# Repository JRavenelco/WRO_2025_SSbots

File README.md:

# Introduction

We are the SSBots team from Mexico, competitors in the WRO Future Engineers category. This is our first year competing in this category, exploring further into WRO after competing for years in the Robo Mission Category. The purpose of this repository is to document our efforts during the 2025 season.

## The team
>Team members
- Sebastian Esquivel
- Santiago Mansilla
>Coach
- Luis Ernesto Fernandez Rodriguez

## Past experiences

  **Our team has participated in WRO Robo Mission competitions for a few years,** as to explore further into new challenges like autonomous vehicles and artificial vision,  we could carry over developments from **RoboMission** . Some of the topics were:
  - Vehicle design and instrumentation, (embedding sensors and actuators while designing purpose built hardware for the specific task.
  - Coding experience, like making a framework, carrying over and porting Python and C code for the LEGO Mindstorms.
  - PID control, implementation and tuning.
  - Path planning, obstacle detection and avoidance. 

Even though we faced multiple difficulties with development and integration of new technologies onto our Robot, while exploring onto the use of electronics for hardware design and training our own AI model for real-time vision, object detection and labeling, and decision making, in addition to all the difficulties that are still to come, we have managed to overcome these difficulties and solve this challenges. We plan on innovating and improving even further before participating in Mexico´s national WRO Future Engineers 2025 competition.

# Engineering Materials

This repository holds the engineering materials developed for a self-driving vehicle with Ackerman drive train for the WRO Future Engineers competition for the 2025 season, documentation will be updated as development continues.   

# Content

* `t-photos` includes team photos during the weekly development workshops
* `v-photos` includes photos of the vehicle, for reference all sides are documented along with a 3D model rendering.
* `video` includes test videos of the vehicle in action and of the development process.
* `schemes` contains schematic diagrams of the electromechanical components, connection diagrams and list of components used in case any other team wants to take inspiration or reproduce the vehicle after the season.
* `src` contains the control software code for all components programmed for the competition.
* `models` contains 3D models of custom components developed, all can be fabricated by use of a 3D printer or laser cutter. As reference a Brick link Studio Model and the STL files for the Technic compatible elements is included.
* `other` contains additional reference files and documentation used for development.

## Teamwork

We usually met up once a week to work on this project, each taking on one part of the project to develop, even if we were not all available, we established targets and tasks to achieve for the current and next couple of weeks. We strived to have everyone involved on all areas of the project, with each dedicated onto the parts they were the most familiar or wanted to further explore and the rest supporting and keeping on the loop as to have the complete picture of the development process. Efforts were documented locally on the computers dedicated for each teams use and pushed onto **GitHub** when significant advances were made or a stable version was reached and frequent communication over the teams chat group. As each part needed to be integrated onto the robot, all our efforts needed to be integrated as a team.  
  
# Conclusion
Looking back on this project, **it’s crazy to see how much we’ve learned.** We started off feeling a little lost, but as we worked through the challenges, we gained a better understanding of how to use these new technologies and integrating them together. We definitely faced some tough moments, but pushing through those helped us grow as a team and as individuals. Even though there’s still a lot more to learn, we’re proud of what we accomplished and excited to take what we’ve learned into future projects.

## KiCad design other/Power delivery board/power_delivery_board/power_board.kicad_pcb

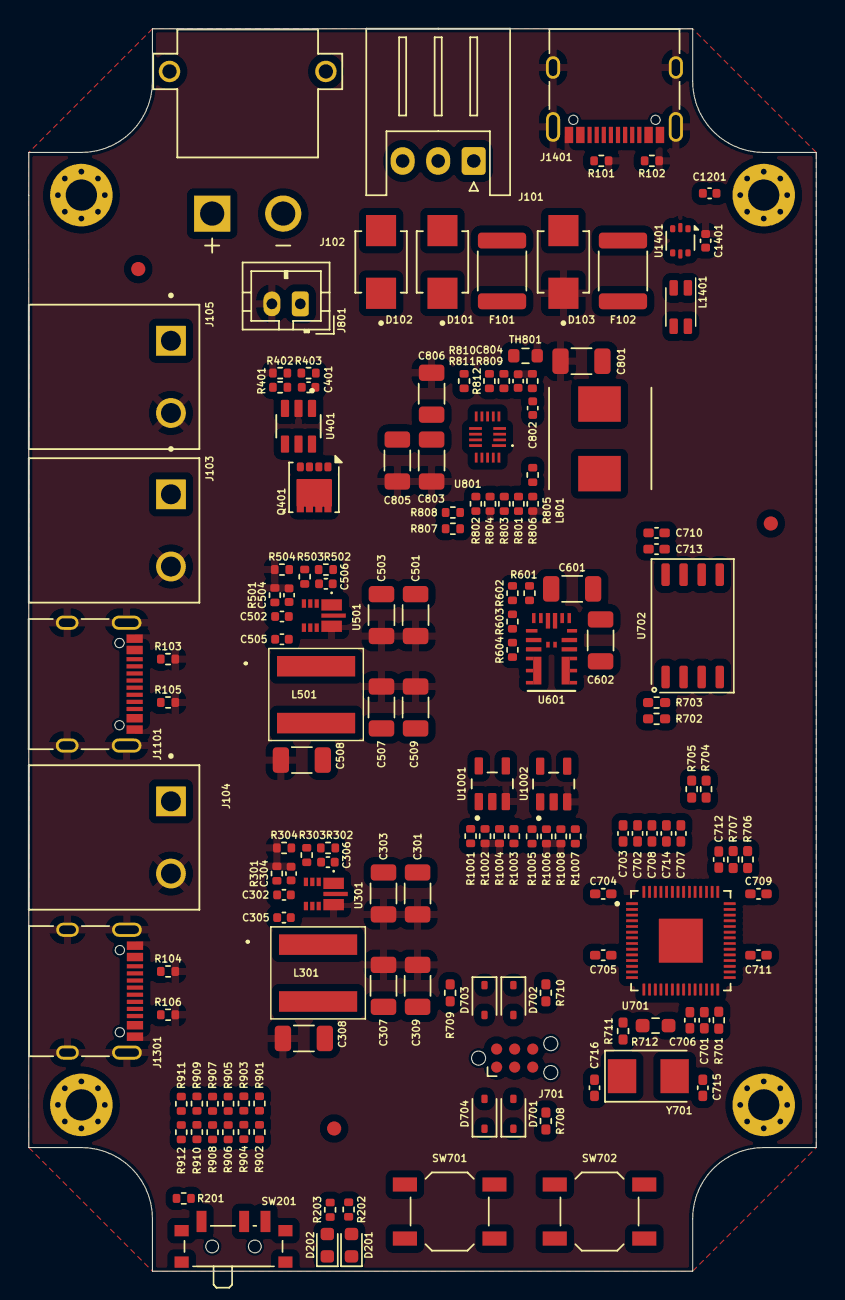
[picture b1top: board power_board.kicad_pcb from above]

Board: 4 copper layers, 55.4 x 87.4 mm, 161 parts (0 on the bottom side), 103 nets, no tracks yet.

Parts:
C301, C303, C501, C503, C601, C801: 10uF 25V; C_1206_3216Metric
C302, C502: 3.3nF; C_0402_1005Metric
C304, C306, C504, C506: NP; C_0402_1005Metric
C305, C401, C505, C802, C1201, C1401: 0.1uF; C_0402_1005Metric
C307, C308, C309, C507, C508, C509, C602: 22uF 16V; C_1206_3216Metric
C701, C702, C704, C705, C706, C707, C708, C709, C711, C713: 0.1uF; C_0402_1005Metric_Pad0.74x0.62mm_HandSolder
C703, C710, C712, C714: 2.2uF; C_0402_1005Metric_Pad0.74x0.62mm_HandSolder
C715, C716: 15pF; C_0402_1005Metric_Pad0.74x0.62mm_HandSolder
C803, C805, C806: 22uF 25V; C_1206_3216Metric
C804: 1uF 10V; C_0402_1005Metric
D101, D103: SZP6SMB10AT3G; DIOM4336X265N
D102: SZP6SMB6.8AT3G; DIOM4336X265N
D201, D202: LED; LED_0603_1608Metric
D701, D702, D703, D704: PESD3V3L1BA; D_SOD-323
F101, F102: Polyfuse; Fuse_1812_4532Metric
FID1201, FID1202, FID1203: Fiducial; Fiducial_1mm_Mask2mm
H1201, H1202, H1203, H1204: MountingHole_Pad; MountingHole_2.2mm_M2_Pad_Via
J101: Conn_01x03_Pin; JST_XH_S3B-XH-A_1x03_P2.50mm_Horizontal
J102: XT30PW-M; AMASS_XT30PW-M
J103, J104, J105: Conn_01x02_Socket; PHOENIX_1759017
J701: Conn_02x03_Odd_Even; Tag-Connect_TC2030-IDC-NL_2x03_P1.27mm_Vertical
J801: Conn_01x02_Socket; JST_PH_B2B-PH-K_1x02_P2.00mm_Vertical
J1101, J1301, J1401: USB_C_Receptacle_USB2.0; USB_C_Receptacle_XKB_U262-16XN-4BVC11
L301, L501: 6.8uH (74439346068); 74439346068
L801: 1.5uH (744311150); WE-HCI_7030_7040_705023
L1401: EMTEK CMF3216F-900M-2P-T; L_CommonMode_Wurth_WE-CNSW-1206
Q401: CSD18543Q3A; VSON-8_3.3x3.3mm_P0.65mm_NexFET
R101, R102, R103, R104, R105, R106, R201, R402, R601, R801, R802, R803, R804, R806, R807, R808, R901, R903, R907, R909, R911, R1001, R1002, R1003, R1004, R1005, R1006, R1007, R1008: 10k; R_0402_1005Metric
R202, R203: 1k; R_0402_1005Metric
R301, R501: 39k; R_0402_1005Metric
R302, R401, R403, R502, R812: 0E; R_0402_1005Metric
R303, R503: 158k; R_0402_1005Metric
R304, R504, R805: 30k; R_0402_1005Metric
R602: 33k; R_0402_1005Metric
R603: 75k; R_0402_1005Metric
R604, R906: 24k; R_0402_1005Metric
R701, R703: 10k; R_0402_1005Metric_Pad0.72x0.64mm_HandSolder
R702, R711: 1k; R_0402_1005Metric_Pad0.72x0.64mm_HandSolder
R704, R705: 27E; R_0402_1005Metric_Pad0.72x0.64mm_HandSolder
R706: 200E; R_0402_1005Metric_Pad0.72x0.64mm_HandSolder
R707: 1E; R_0402_1005Metric_Pad0.72x0.64mm_HandSolder
R708, R709, R710: 50E; R_0402_1005Metric_Pad0.72x0.64mm_HandSolder
R712: NP; R_0603_1608Metric_Pad0.98x0.95mm_HandSolder
R809, R902, R904, R905, R908: 6.2k; R_0402_1005Metric
R810: 12k; R_0402_1005Metric
R811: 3.3k; R_0402_1005Metric
R910: NP; R_0402_1005Metric
R912: 20k; R_0402_1005Metric
SW201: SW_SPST; SW_SPDT_PCM12
SW701, SW702: SW_SPST; SW_SPST_TL3342
TH801: Thermistor_NTC_US; R_0603_1608Metric
U301, U501: AP63357QZV-7; CONV_AP63357QZV-7
U401: LM74700QDBVRQ1; SOT95P280X145-6N
U601: MPM3606GQV-P; QFN3p0x5p0x1p6_MPM3606_MNP
U701: RP2040; QFN40P700X700X90-57N
U702: W25Q128JVS; SOIC-8_5.23x5.23mm_P1.27mm
U801: MP2672AGD-0000-P; MP2672AGD0000P
U1001, U1002: 74AHC1G08; SOT95P280X145-5N
U1401: USBLC6-2P6; SOT-666
Y701: Crystal 12MHz; Crystal_SMD_5032-2Pin_5.0x3.2mm

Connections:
+1V1_HOST_MCU: C701.1, C702.1, C703.1, U701.23 (DVDD), U701.45 (VREG_VOUT), U701.50 (DVDD)
+3V3_HOST_MCU: C704.1, C705.1, C706.1, C707.1, C708.1, C709.1, C710.1, C711.1, C713.1, C714.1, D704.2 (A2), J701.1, R701.1, R703.1, R706.1, U701.1 (IOVDD), U701.10 (IOVDD), U701.22 (IOVDD), U701.33 (IOVDD), U701.42 (IOVDD), U701.44 (VREG_VIN), U701.48 (USB_VDD), U701.49 (IOVDD), U702.8 (VCC)
/PI_USB_H_N: L1401.2, R704.2
/PI_USB_H_P: L1401.4, R705.2
/POWER_SUPPLY/BATTERY_CHARGER/SCL_BATTERY_CHARGER: R808.1, U701.31 (GPIO20), U801.14 (SCL)
/POWER_SUPPLY/BATTERY_CHARGER/SDA_BATTERY_CHARGER: R807.1, U701.30 (GPIO19), U801.15 (SDA)
/POWER_SUPPLY/BAT_MID: D102.2 (A2), J101.2, R812.1, R905.1
/POWER_SUPPLY/BAT_MID_MON: R905.2, R906.1, U701.4 (GPIO2)
/POWER_SUPPLY/BAT_PLUS: C601.1, C806.1, F101.2, R601.1, R903.1, U601.16 (IN), U801.10 (BATT)
/POWER_SUPPLY/BAT_PLUS_MON: R903.2, R904.1, U701.3 (GPIO1)
/POWER_SUPPLY/BAT_SYS: C401.1, C803.1, C805.1, Q401.1 (S), Q401.2 (S), Q401.3 (S), R403.1, R907.1, U401.6 (ANODE), U801.11 (SYS)
/POWER_SUPPLY/BAT_SYS_MON: R907.2, R908.1, U701.5 (GPIO3)
/POWER_SUPPLY/CHG_IN: C801.1, F102.2, L801.1, R805.1, R901.1, U801.1 (IN)
/POWER_SUPPLY/CHG_INDICATOR: D202.1 (K), U701.27 (GPIO16)
/POWER_SUPPLY/CHG_IN_MON: R901.2, R902.1, U701.2 (GPIO0)
/POWER_SUPPLY/CHG_IN_VALID: R801.2, U701.11 (GPIO8), U801.18 (~ACOK)
/POWER_SUPPLY/CHG_STAT: R802.2, R1001.2, R1002.1, U701.9 (GPIO7), U801.16 (~STAT), U1001.1
/POWER_SUPPLY/HOST_MCU/GPIO_14: R201.2, SW201.1 (A), U701.17 (GPIO14)
/POWER_SUPPLY/HOST_MCU/QSPI_CS: R702.2, R703.2, U701.56 (QSPI_CSN), U702.1 (~CS)
/POWER_SUPPLY/HOST_MCU/QSPI_SCK: U701.52 (QSPI_SCLK), U702.6 (CLK)
/POWER_SUPPLY/HOST_MCU/QSPI_SD0: U701.53 (QSPI_SD0), U702.5 (DI(IO0))
/POWER_SUPPLY/HOST_MCU/QSPI_SD1: U701.55 (QSPI_SD1), U702.2 (DO(IO1))
/POWER_SUPPLY/HOST_MCU/QSPI_SD2: U701.54 (QSPI_SD2), U702.3 (IO2)
/POWER_SUPPLY/HOST_MCU/QSPI_SD3: U701.51 (QSPI_SD3), U702.7 (IO3)
/POWER_SUPPLY/HOST_MCU/RUN: R701.2, R708.1, SW701.1 (A), U701.26 (RUN)
/POWER_SUPPLY/HOST_MCU/SWCLK: R710.2, U701.24 (SWCLK)
/POWER_SUPPLY/HOST_MCU/SWDIO: R709.2, U701.25 (SWD)
/POWER_SUPPLY/HOST_MCU/USB_BOOT: R702.1, SW702.2 (B)
/POWER_SUPPLY/HOST_MCU/USB_MCU_D+: R705.1, U701.47 (USB_DP)
/POWER_SUPPLY/HOST_MCU/USB_MCU_D-: R704.1, U701.46 (USB_DM)
/POWER_SUPPLY/HOST_MCU/XIN: R711.2, R712.1, U701.20 (XIN)
/POWER_SUPPLY/HOST_MCU/XOUT: C715.2, R712.2, U701.21 (XOUT), Y701.2
/POWER_SUPPLY/PWR_INDICATOR: D201.1 (K), U701.18 (GPIO15)
/POWER_SUPPLY/PWR_VCC_REGOUT_MON: R909.2, R910.1, U701.7 (GPIO5)
/POWER_SUPPLY/PWR_VDD_REGOUT_MON: R911.2, R912.1, U701.6 (GPIO4)
/POWER_SUPPLY/REG_ENABLE_0: U301.2 (EN), U701.15 (GPIO12)
/POWER_SUPPLY/REG_ENABLE_1: U501.2 (EN), U1002.4
/POWER_SUPPLY/REG_ENABLE_1_HOST: R1005.2, R1006.1, U701.16 (GPIO13), U1002.1
/POWER_SUPPLY/REG_PGOOD_0: R1007.2, R1008.1, U301.5 (PG), U701.12 (GPIO9), U1002.2
/POWER_SUPPLY/REG_PGOOD_1: U501.5 (PG), U701.13 (GPIO10)
/POWER_SUPPLY/SW_ENABLE: R401.2, U1001.4
/POWER_SUPPLY/SW_ENABLE_HOST: R1003.2, R1004.1, U701.14 (GPIO11), U1001.2
/USB_C_CONN1/USB_CMC_D+: L1401.3, U1401.4 (I/O2)
/USB_C_CONN1/USB_CMC_D-: L1401.1, U1401.6 (I/O1)
/USB_C_CONN1/USB_CONN_CC1_USB_C_CONN1: J1401.A5 (CC1), R102.1
/USB_C_CONN1/USB_CONN_CC2_USB_C_CONN1: J1401.B5 (CC2), R101.1
/USB_C_CONN1/USB_CONN_D+: J1401.A6 (D+), J1401.B6 (D+), U1401.3 (I/O2)
/USB_C_CONN1/USB_CONN_D-: J1401.A7 (D-), J1401.B7 (D-), U1401.1 (I/O1)
/USB_C_CONN2/USB_CONN_CC1_USB_C_CONN2: J1101.A5 (CC1), R103.1
/USB_C_CONN2/USB_CONN_CC2_USB_C_CONN2: J1101.B5 (CC2), R105.1
/USB_C_CONN2/USB_CONN_D+: J1101.A6 (D+), J1101.B6 (D+)
/USB_C_CONN2/USB_CONN_D-: J1101.A7 (D-), J1101.B7 (D-)
/USB_C_CONN3/USB_CONN_CC1_USB_C_CONN3: J1301.A5 (CC1), R104.1
/USB_C_CONN3/USB_CONN_CC2_USB_C_CONN3: J1301.B5 (CC2), R106.1
/USB_C_CONN3/USB_CONN_D+: J1301.A6 (D+), J1301.B6 (D+)
/USB_C_CONN3/USB_CONN_D-: J1301.A7 (D-), J1301.B7 (D-)
DVCC: C306.1, C307.1, C308.1, C309.1, J103.1, J1101.A4 (VBUS), J1101.A9 (VBUS), J1101.B4 (VBUS), J1101.B9 (VBUS), L301.2, R302.1
DVDD: C506.1, C507.1, C508.1, C509.1, J104.1, J1301.A4 (VBUS), J1301.A9 (VBUS), J1301.B4 (VBUS), J1301.B9 (VBUS), L501.2, R502.1
GND: C301.2, C303.2, C304.2, C307.2, C308.2, C309.2, C501.2, C503.2, C504.2, C507.2, C508.2, C509.2, C801.2, C803.2, C804.2, C805.2, C806.2, C1401.2, D103.1 (A1), J103.2, J104.2, J105.2, J801.2, J1101.A1 (GND), J1101.A12 (GND), J1101.B1 (GND), J1101.B12 (GND), J1101.S1 (SHIELD), J1301.A1 (GND), J1301.A12 (GND), J1301.B1 (GND), J1301.B12 (GND), J1301.S1 (SHIELD), J1401.A1 (GND), J1401.A12 (GND), J1401.B1 (GND), J1401.B12 (GND), J1401.S1 (SHIELD), R101.2, R102.2, R103.2, R104.2, R105.2, R106.2, R301.2, R304.2, R402.2, R501.2, R504.2, R804.2, R806.2, R809.2, R1002.2, R1004.2, R1006.2, R1008.2, TH801.2, U301.8 (GND), U401.2 (GND), U501.8 (GND), U801.6 (AGND), U801.13 (PGND), U1001.3 (GND), U1002.3 (GND), U1401.2 (GND)
GND_HOST_MCU: C601.2, C602.2, C701.2, C702.2, C703.2, C704.2, C705.2, C706.2, C707.2, C708.2, C709.2, C710.2, C711.2, C712.2, C713.2, C714.2, C715.1, C716.1, D701.1 (A1), D702.1 (A1), D703.1 (A1), D704.1 (A1), J701.5, R602.2, R604.2, SW201.2 (B), SW701.2 (B), SW702.1 (A), U601.3 (AGND), U601.12 (PGND), U601.13 (PGND), U601.14 (PGND), U701.19 (TESTEN), U701.57 (GND), U702.4 (GND)
GND_MECHANICAL: C1201.1, C1201.2, H1201.1, H1202.1, H1203.1, H1204.1
GND_Root: D101.1 (A1), D102.1 (A1), J101.3, J102.N
unnamed: C302.2, R301.1
unnamed: C502.2, R501.1
unnamed: C716.2, R711.1, Y701.1
unnamed: D101.2 (A2), F101.1, J101.1, J102.P
unnamed: D201.2 (A), R202.2
unnamed: D202.2 (A), R203.2
unnamed: D701.2 (A2), J701.3, R708.2
unnamed: D702.2 (A2), J701.4, R710.1
unnamed: D703.2 (A2), J701.2, R709.1
unnamed: J801.1, R810.2, R811.1, U801.8 (NTC)
unnamed: Q401.4 (G), U401.5 (GATE)
unnamed: R302.2, R303.1
unnamed: R502.2, R503.1
unnamed: R706.2, R707.1
unnamed: R811.2, TH801.1
unnamed: C305.1, U301.6 (BST)
unnamed: C302.1, C304.1, U301.4 (COMP)
unnamed: C306.2, R303.2, R304.1, U301.3 (FB)
unnamed: C305.2, L301.1, U301.9 (SW)
unnamed: R401.1, R402.1, R403.2, U401.3 (EN)
unnamed: C401.2, U401.1 (VCAP)
unnamed: C505.1, U501.6 (BST)
unnamed: C502.1, C504.1, U501.4 (COMP)
unnamed: C506.2, R503.2, R504.1, U501.3 (FB)
unnamed: C505.2, L501.1, U501.9 (SW)
unnamed: R602.1, U601.18 (AAM)
unnamed: R601.2, U601.17 (EN)
unnamed: R603.2, R604.1, U601.1 (FB)
unnamed: C712.1, R707.2, U701.43 (ADC_AVDD)
unnamed: C802.2, U801.3 (BST)
unnamed: R803.2, R804.1, U801.17 (CV)
unnamed: R809.1, U801.5 (ISET)
unnamed: R812.2, U801.9 (MID)
unnamed: C802.1, L801.2, U801.2 (SW_1), U801.12 (SW_2)
unnamed: R805.2, R806.1, U801.7 (VLIM)
PWR_GND: R902.2, R904.2, R906.2, R908.2, R910.2, R912.2
VCC_BATTERY_CHARGER: C804.1, R801.1, R802.1, R803.1, R807.2, R808.2, R810.1, U801.4 (VCC)
VCC_HOST_MCU: C602.1, R201.1, R202.1, R203.1, R603.1, U601.7 (OUT), U601.8 (OUT), U601.9 (OUT)
VCC_REGULATOR_SEQ: R1001.1, R1003.1, R1005.1, R1007.1, U1002.5 (VCC)
VCC_USB_C_CONN1: C1401.1, D103.2 (A2), F102.1, J1401.A4 (VBUS), J1401.A9 (VBUS), J1401.B4 (VBUS), J1401.B9 (VBUS), U1401.5 (VBUS)
VM: C301.1, C303.1, C501.1, C503.1, J105.1, Q401.5 (D), U301.1 (VIN), U401.4 (CATHODE), U501.1 (VIN)

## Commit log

2025-05-04 Initial commit and add xbox-controller-monitor as submodule[D
2025-05-04 Add fan control script and systemd service
2025-05-05 Actualizar README.md
2025-06-01 oak training and interpreter_startup.py
2025-06-01 Updated xbox-controller-monitor submodule
2025-06-07 Backup Jetson Nano previo a migrar a Raspberry Pi 5
2025-06-20 Simplified "interpreter_startup.py"
    Simplified script, originated from "interpreter_startup.py", now called "screenSimplified.py". This new script only sends the commands needed to initialize interpreter mode, without any unnecessary a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
2025-06-20 New base script that only turns around the track
    Now with the screen startup already integrated, but does not follow the wall with ultrasonic sensor yet.
2025-06-21 Minor adjustments (removed resetGyro() after every turn)
2025-06-22 Display OLED para mostrar la SSID y la IP
2025-06-23 Script to take pictures with OAK-D Lite camera, which will later be used for model training
2025-06-23 Modified script to use max resolution possible with the OAK camera (13 MP 4208x3120)
2025-06-23 "small changes"
2025-06-23 Removed parking folder and replaced it with combined folder (redbox+greenbox)
2025-06-24 Added 502 pictures to dataset using Git LFS (251 for greenbox and 251 for redbox)
2025-06-24 Added 500 pictures to combined dataset
2025-06-26 Unrevised changes (temporary backup)
2025-06-27 Added models directory
2025-06-27 Uploaded files of directory, Other
2025-06-27 Added datasheets directory
2025-06-27 Added Game rules directory
2025-06-27 Added Power delivery Board design files
2025-06-27 Added schemes directory
2025-06-27 Added files to v-photos directory
2025-07-15 Create Engineer diary
2025-07-16 Update Engineer diary
    16/7/2025
2025-07-31 Create July 9th
2025-07-31 Add files via upload
    July 9th: This day we tried implementing two-speed automatic gearbox for more torque at first and then more speed, then temporarily removed due to complications (might improve it and use it later).
2025-07-31 Create Reports
2025-07-31 Update Reports
2025-07-31 Update July 9th
2025-09-15 Rename Architecture.png to regional_architecture.png
2025-09-15 Create national_architecture
2025-09-15 Rename robot_architecture.png to national_architecture.png
2025-09-17 Editing README.md
2025-09-17 Test Update README.md
2025-09-17 Create challenge1_jellyfish
2025-09-17 Create Code
2025-09-17 Edited file structure
2025-09-17 Create challenge2_jellyfish
2025-09-17 Update Code
2025-09-17 Auto stash before merge of "main" and "origin/main"
    Moving code files to src
2025-09-19 Actualización día 1 WRO Nacional
